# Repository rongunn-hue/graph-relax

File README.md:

# Graph-Relax

Graph-Relax is experimental research into automatically generating electrically
correct, human-understandable schematic layouts from circuit connectivity.

This repository preserves exploratory placement research, including graph
construction from circuit connectivity, graph planarity experiments, planar
embeddings, connectivity- and nearness-based placement, crossing reduction,
compaction, radial and tent-pole experiments, circular-envelope measurement,
and circular-envelope bulge correction.

The current architectural direction is:

```text
circuit/netlist
    -> abstract graph
    -> determine planar/nonplanar
    -> analyze connectivity/nearness
    -> intelligent initial placement
    -> geometric relaxation/compaction
    -> eventual schematic representation
```

This is research and prototype code, not a finished schematic generator.

## Graph placement invariant

Every new graph coordinate generator must pass its raw coordinates through
`placement_geometry.enforce_minimum_node_spacing` before generic geometry
validation and serialization. The shared `MIN_NODE_DISTANCE` is enforced by a
single uniform scale about the placement anchor, preserving angles, relative
distance ratios, aspect ratio, cyclic orientation, and crossing topology.
Coincident distinct vertices are a placement failure because uniform scaling
cannot separate them. Vertex-on-unrelated-edge cases are reported separately;
minimum node spacing does not prevent collinearity.

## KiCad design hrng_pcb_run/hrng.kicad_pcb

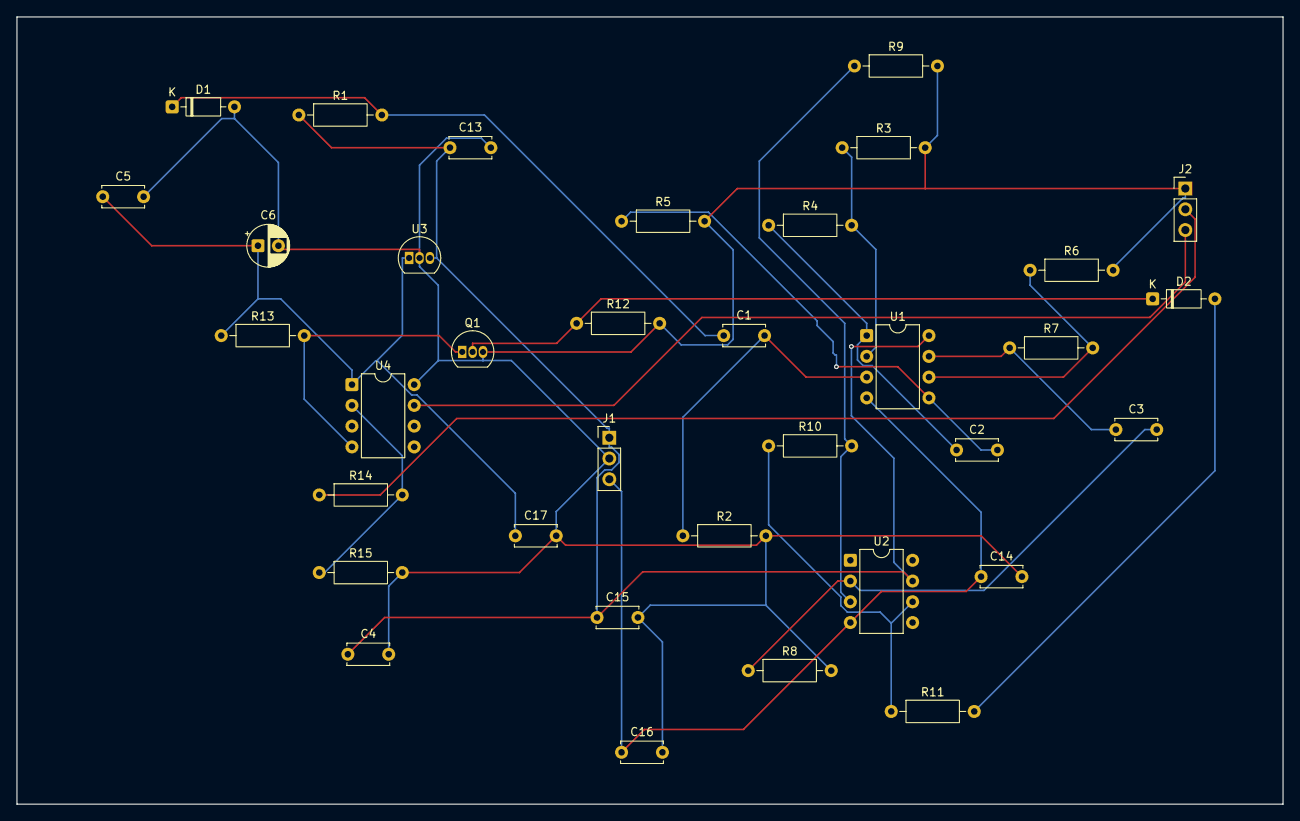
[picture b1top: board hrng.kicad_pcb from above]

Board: 2 copper layers, 155.0 x 96.3 mm, 35 parts (0 on the bottom side), 20 nets.

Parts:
C1, C2, C3, C4, C5, C13, C14, C15, C16, C17: GENERIC_CAPACITOR; C_Disc_D5.0mm_W2.5mm_P5.00mm
C6: GENERIC_CAPACITOR; CP_Radial_D5.0mm_P2.50mm
D1: ZENER_2PIN; D_DO-35_SOD27_P7.62mm_Horizontal
D2: 1N4148; D_DO-35_SOD27_P7.62mm_Horizontal
J1, J2: GENERIC_CONNECTOR_3; PinHeader_1x03_P2.54mm_Vertical
Q1: P2N2222A; TO-92_Inline
R1, R2, R3, R4, R5, R6, R7, R8, R9, R10, R11, R12, R13, R14, R15: GENERIC_RESISTOR; R_Axial_DIN0207_L6.3mm_D2.5mm_P10.16mm_Horizontal
U1: LM1458; DIP-8_W7.62mm
U2: LM741; DIP-8_W7.62mm
U3: WS78L05; TO-92_Inline
U4: PICAXE_08M2; DIP-8_W7.62mm

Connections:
0V: C4.2, C5.2, C6.2, C13.2, C14.2, C15.2, C16.2, C17.2, D1.2, J1.2, J2.1, Q1.3, R2.2, R3.2, R5.2, R6.2, R8.2, R9.2, R12.2, R15.2, U3.2, U4.8
+5V: C5.1, C6.1, C17.1, R13.1, U3.1, U4.1
+9V: C4.1, C13.1, C15.1, J1.1, R1.1, U1.8, U2.7, U3.3
-9V: C14.1, C16.1, J1.3, U1.4, U2.4
D2_ANODE: D2.2, R11.2
NOISE_RAW: C1.1, D1.1, R1.2
PROG_IN: J2.2, R14.1
Q1_BASE: D2.1, Q1.2, R12.1
RNG_RAW: Q1.1, R13.2, U4.4
SERIAL_IN: R14.2, R15.1, U4.2
SERIAL_OUT: J2.3, U4.7
U1A_MINUS: R3.1, R4.2, U1.2
U1A_OUT: C2.1, R4.1, U1.1
U1A_PLUS: C1.2, R2.1, U1.3
U1B_MINUS: R6.1, R7.2, U1.6
U1B_OUT: C3.1, R7.1, U1.7
U1B_PLUS: C2.2, R5.1, U1.5
U2_MINUS: C3.2, R8.1, U2.2
U2_OUT: R10.1, R11.1, U2.6
U2_PLUS: R9.1, R10.2, U2.3

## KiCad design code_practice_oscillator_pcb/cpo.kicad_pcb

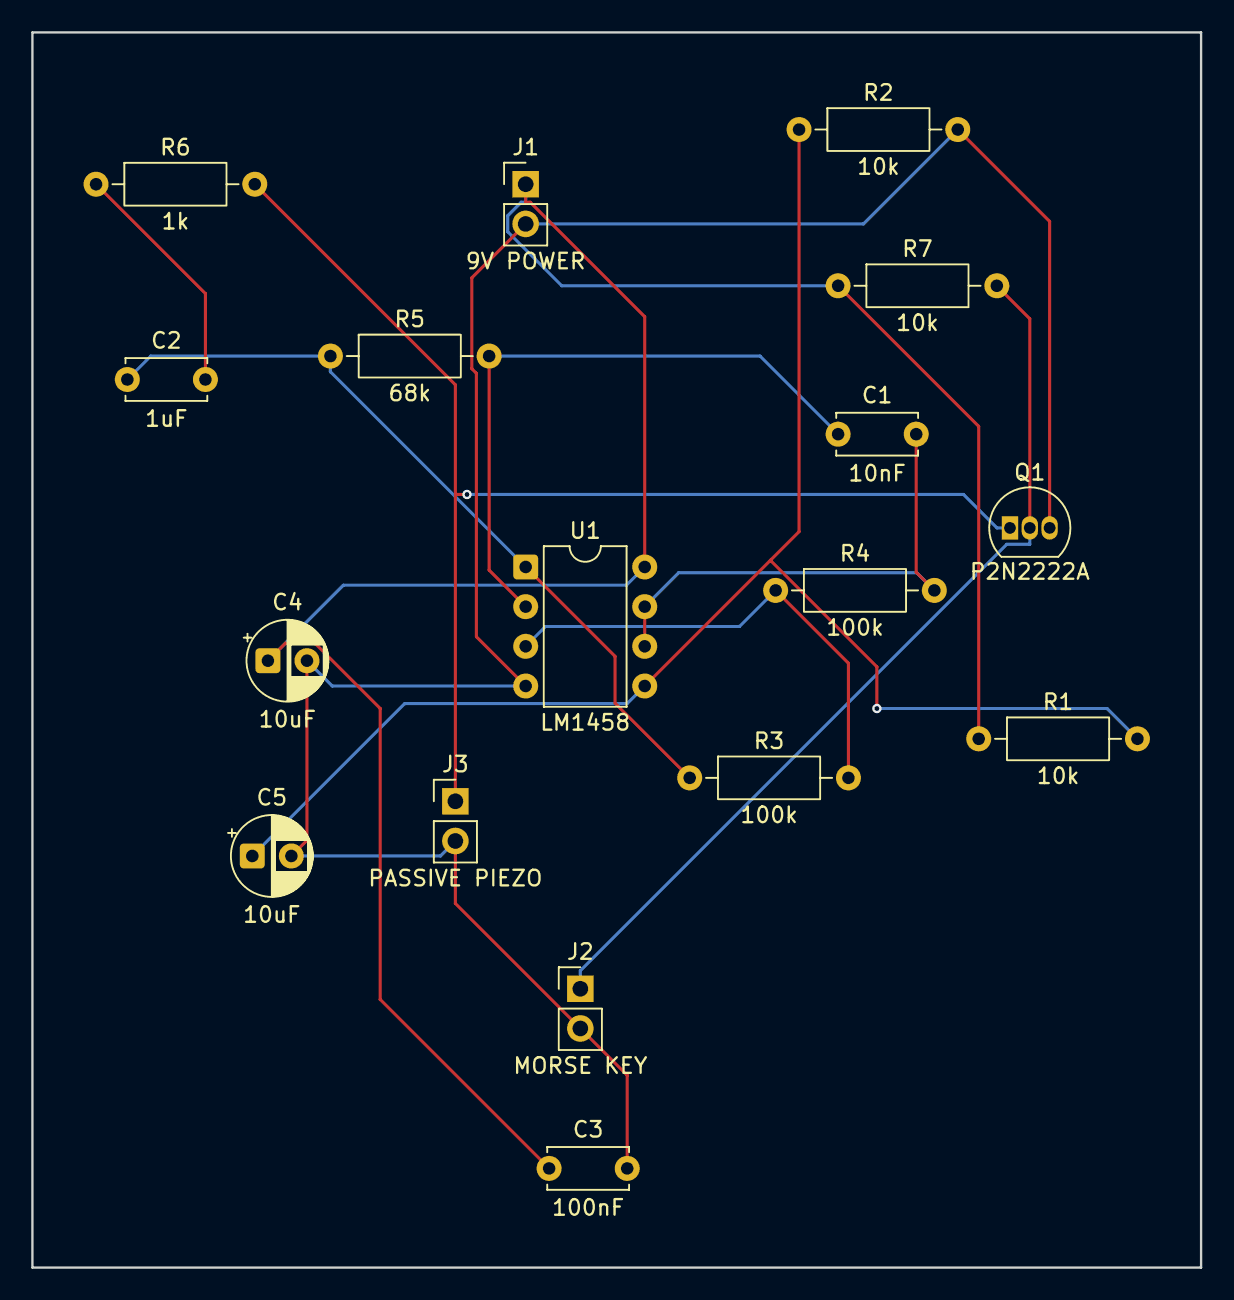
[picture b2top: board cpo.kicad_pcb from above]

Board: 2 copper layers, 74.8 x 79.1 mm, 17 parts (0 on the bottom side), 10 nets.

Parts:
C1: 10nF; C_Disc_D5.0mm_W2.5mm_P5.00mm
C2: 1uF; C_Disc_D5.0mm_W2.5mm_P5.00mm
C3: 100nF; C_Disc_D5.0mm_W2.5mm_P5.00mm
C4, C5: 10uF; CP_Radial_D5.0mm_P2.50mm
J1: 9V POWER; PinHeader_1x02_P2.54mm_Vertical
J2: MORSE KEY; PinHeader_1x02_P2.54mm_Vertical
J3: PASSIVE PIEZO; PinHeader_1x02_P2.54mm_Vertical
Q1: P2N2222A; TO-92_Inline
R1, R2, R7: 10k; R_Axial_DIN0207_L6.3mm_D2.5mm_P10.16mm_Horizontal
R3, R4: 100k; R_Axial_DIN0207_L6.3mm_D2.5mm_P10.16mm_Horizontal
R5: 68k; R_Axial_DIN0207_L6.3mm_D2.5mm_P10.16mm_Horizontal
R6: 1k; R_Axial_DIN0207_L6.3mm_D2.5mm_P10.16mm_Horizontal
U1: LM1458; DIP-8_W7.62mm

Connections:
+9V: C3.1, C4.1, J1.1, R1.1, R7.1, U1.8
AUDIO_FEED: C2.2, R6.1
AUDIO_OUT: J3.1, Q1.1, R6.2
GND: C3.2, C4.2, C5.2, J1.2, J2.2, J3.2, Q1.3, R2.2, U1.4
KEY_CTRL: J2.1, Q1.2, R7.2
OSC_MINUS: C1.1, R5.2, U1.2
OSC_OUT: C2.1, R3.1, R5.1, U1.1
OSC_PLUS: R3.2, R4.1, U1.3
VREF: C1.2, R4.2, U1.6, U1.7
VREF_DIV: C5.1, R1.2, R2.1, U1.5
